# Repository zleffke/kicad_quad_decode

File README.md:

# kicad_quad_decode
Quadrature feedback decoder for Spid RAS/HR Rotator

Single Channel Version is a prototype of the circuit.

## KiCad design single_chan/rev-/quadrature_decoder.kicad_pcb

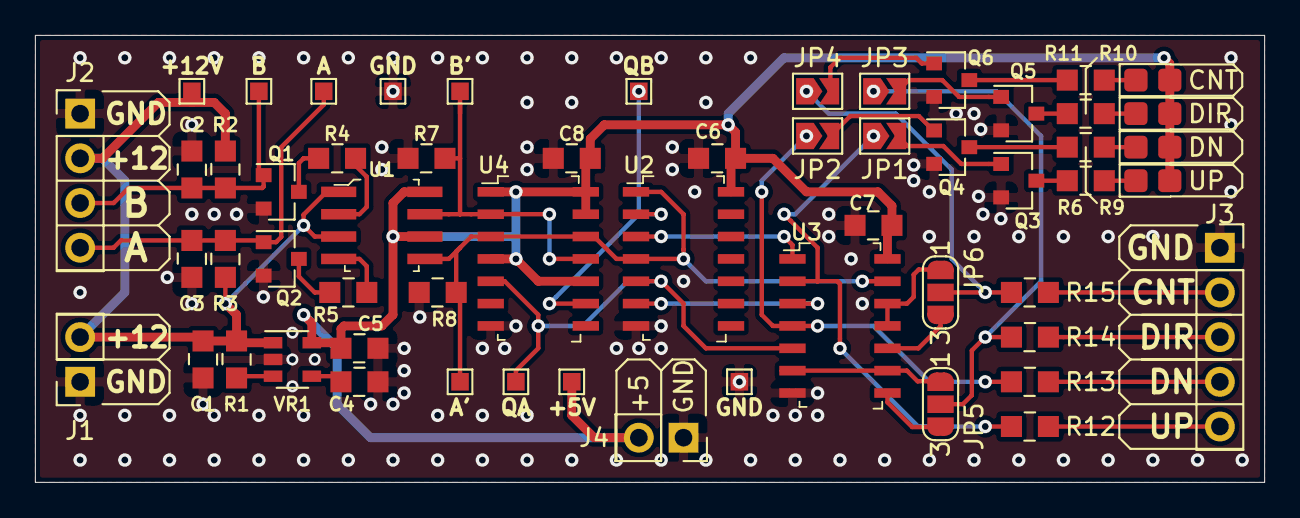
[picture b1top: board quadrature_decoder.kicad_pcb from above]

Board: 2 copper layers, 69.8 x 25.4 mm, 58 parts (0 on the bottom side), 41 nets.

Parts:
+5V, +12V: TestPoint; TestPoint_Pad_1.0x1.0mm
A: TestPoint; TestPoint_Pad_1.0x1.0mm
A': TestPoint; TestPoint_Pad_1.0x1.0mm
B: TestPoint; TestPoint_Pad_1.0x1.0mm
B': TestPoint; TestPoint_Pad_1.0x1.0mm
C1: 10uF; 0805
C2, C3, C4, C5, C6, C7, C8: 1uF; 0805
D1: UP; LED_0805_2012Metric_Castellated
D2: DN; LED_0805_2012Metric_Castellated
D3: DIR; LED_0805_2012Metric_Castellated
D4: CNT; LED_0805_2012Metric_Castellated
GND: TestPoint; TestPoint_Pad_1.0x1.0mm
GND#2: TestPoint; TestPoint_Pad_1.0x1.0mm
J1: Power; PinSocket_1x02_P2.54mm_Vertical
J2: Quad; PinHeader_1x04_P2.54mm_Vertical
J3: Output; PinSocket_1x05_P2.54mm_Vertical
J4: 5V_OUT; PinSocket_1x02_P2.54mm_Vertical
JP1, JP2, JP3, JP4: SJB; SolderJumper-2_P1.3mm_Open_TrianglePad1.0x1.5mm
JP5, JP6: SJB; SolderJumper-3_P1.3mm_Open_RoundedPad1.0x1.5mm_NumberLabels
Q1, Q2, Q3, Q4, Q5, Q6: DMG3414U; SOT-23
QA: TestPoint; TestPoint_Pad_1.0x1.0mm
QB: TestPoint; TestPoint_Pad_1.0x1.0mm
R1, R2, R3: 100k; 0805
R4, R5, R12, R13, R14, R15: 1k; 0805
R6, R9, R10, R11: 220; 0805
R7, R8: 10k; 0805
U1: ILD207T; SOIC-8_W3.9mm
U2: 74HC00; SOIC-14_W3.9mm
U3: 74AHC04; SOIC-14_W3.9mm
U4: 74HC74; SOIC-14_W3.9mm
VR1: SPX3819M5-L-5-0; SOT-23-5

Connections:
+5V: +5V.1, C5.1, C6.1, C7.2, C8.2, D1.2, D2.2, D3.2, D4.2, J4.2, U1.6, U1.8, U2.14, U3.14, U4.1, U4.4, U4.10, U4.13, U4.14, VR1.5
+12V: +12V.1, C1.1, J1.2, J2.2, R1.1, R2.1, R3.1, U1.1, U1.3, VR1.1
/A: A.1, C3.1, J2.4, Q2.1, R3.2
/B: B.1, C2.1, J2.3, Q1.1, R2.2
/COUNT: J3.2, R15.2
/DIR: J3.3, R14.2
/DN(CCW): J3.4, R13.2
/UP(CW): J3.5, R12.2
/cnt: JP4.1, JP6.2, R15.1
/dir: JP3.1, JP5.2, R14.1
/dn: JP2.1, R13.1, U3.4
/up: JP1.1, R12.1, U3.2
GND: C1.2, C2.2, C3.2, C4.2, C5.2, C6.2, C7.1, C8.1, GND.1, GND#2.1, J1.1, J2.1, J3.1, J4.1, Q1.2, Q2.2, Q3.2, Q4.2, Q5.2, Q6.2, R7.1, R8.1, U2.7, U3.7, U4.7, VR1.2
unnamed: C4.1, VR1.4
unnamed: D1.1, R6.2
unnamed: D2.1, R9.2
unnamed: D3.1, R10.2
unnamed: D4.1, R11.2
unnamed: JP1.2, Q3.1
unnamed: JP2.2, Q4.1
unnamed: JP3.2, Q5.1
unnamed: JP4.2, Q6.1
unnamed: JP5.1, U3.6, U3.9
unnamed: JP5.3, U3.8
unnamed: JP6.1, U3.11, U3.12
unnamed: JP6.3, U3.10
unnamed: Q1.3, R4.2
unnamed: Q2.3, R5.2
unnamed: Q3.3, R6.1
unnamed: Q4.3, R9.1
unnamed: Q5.3, R10.1
unnamed: Q6.3, R11.1
unnamed: R1.2, VR1.3
unnamed: R4.1, U1.2
unnamed: R5.1, U1.4
unnamed: B'.1, R7.2, U1.7, U4.2, U4.11
unnamed: A'.1, R8.2, U1.5, U2.1, U2.4, U3.13, U4.3, U4.12
unnamed: QB.1, U2.2, U4.9
unnamed: QA.1, U2.5, U3.5, U4.5
unnamed: U2.3, U3.1
unnamed: U2.6, U3.3

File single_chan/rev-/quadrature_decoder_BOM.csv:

Ref,Qnty,Value,Footprint,Description,Link
"C1, ",1,10uF,digikey-footprints:0805,Unpolarized capacitor,
"C2, C3, C6, C7, C5, C8, C4, ",7,1uF,digikey-footprints:0805,Unpolarized capacitor,
"D1, ",1,UP,LED_SMD:LED_0805_2012Metric_Castellated,Light emitting diode,
"D2, ",1,DN,LED_SMD:LED_0805_2012Metric_Castellated,Light emitting diode,
"D3, ",1,DIR,LED_SMD:LED_0805_2012Metric_Castellated,Light emitting diode,
"D4, ",1,CNT,LED_SMD:LED_0805_2012Metric_Castellated,Light emitting diode,
"Q2, Q1, Q3, Q6, Q5, Q4, ",6,DMG3414U,Package_TO_SOT_SMD:SOT-23,"4.2A Id, 20V Vds, N-Channel MOSFET, SOT-23",
"R3, R2, R1, ",3,100k,digikey-footprints:0805,"Resistor, US symbol",
"R5, R12, R13, R14, R15, R4, ",6,1k,digikey-footprints:0805,"Resistor, US symbol",
"R6, R9, R10, R11, ",4,220,digikey-footprints:0805,"Resistor, US symbol",
"R7, R8, ",2,10k,digikey-footprints:0805,"Resistor, US symbol",
"U1, ",1,ILD207T,digikey-footprints:SOIC-8_W3.9mm,OPTOISOLTR 4KV 2CH TRANS 8-SOIC,LINK
"U2, ",1,74HC00,digikey-footprints:SOIC-14_W3.9mm,quad 2-input NAND gate,LINK
"U3, ",1,74AHC04,digikey-footprints:SOIC-14_W3.9mm,Hex Inverter,LINK
"U4, ",1,74HC74,digikey-footprints:SOIC-14_W3.9mm,"Dual D Flip-flop, Set & Reset",LINK
"VR1, ",1,SPX3819M5-L-5-0,Package_TO_SOT_SMD:SOT-23-5,"500mA Low drop-out regulator, Fixed Output 5.0V, SOT-23-5",LINK

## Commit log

2019-11-03 adding single channel, rev-, quad decoder. This commit was purchased from Osh Park.
2019-11-03 adding pdf of schematic
2019-11-03 added BOM

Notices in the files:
single_chan/rev-/quadrature_decoder.kicad_pcb:
License: CC BY 4.0
